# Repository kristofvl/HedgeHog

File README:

More information about this package can currently be found at:
 http://kristofvl.github.io/HedgeHog/ 

****************************************************************

In short, this repository contains three packages:

1. The HedgeHog firmware (operating system), requires:
    - MPLAB X (free IDE, download from Microchip.com)
    - Microchip Application Library (free library set, download 
      from Microchip.com)

2. The HedgeHog Graphical interface software, requires:
    - the basic python libraries
    - matplotlib

3. The hardware design files for the HedgeHog sensor, requires:
    - eagleCAD (free PCB design tool, download from 
      CadSoftusa.com)

****************************************************************

# User Manual

## Setup a new HedgeHog

There are four basic interactions, that you can do with your HedgeHog

	- Configure the HedgeHog
	- Start logging
	- Download the logged data
	- Display the downloaded data

In order to perform this actions, you first need to setupt your PC properly.

	- Clone this repository
	- Execute the command *./install_HHG.py* in *~/HedgeHog/HHG*

This will create a few Desktop shortcuts to scripts, that will be discussed later on.

If you have a brand new HedgeHog, you will need to do some extra adjustments, if not, then just continue at *Configure the HedgeHog*. The following instructions might also help, if there are other issues with the HedgeHog. You need to put the right image on the SD-Card. To do this, put the SD-Card in the SD-Card slot in yout PC. You need to find out, where the SD-Card is mounted (e.g. with *dmesg*). In this example, it is assumed, the SD-Card is mounted at /dev/sdc. Go to the folder *~/HedgeHog/HHG/dd_img/* and execute the commands

	- *sudo dd if=dd.img of=/dev/sdc*
	- *sync*

This will export the correct image to the SD-Card. After exporting the image, disconnect the SD-Card and reconnect it again. If it is named *HEDGHG*, the export was succesfull. Now put your SD-Card into your HedgeHog.

Now you need to flash the HedgeHog with *MPLab*. Make sure to choose the correct hardware profile.

## Configure the HedgeHog

If you plug in the HedgeHog into the USB-Connector of your PC, it should be recognized correctly now. The install command has created a shortcut to the configuration script. Start the script now and choose the configuration you want, then click *configure*. The HedgeHog will unmount and then mount again by itself. As soon as the HedgeHog is mounted again, the configuration is applied.

## Start logging

When the HedgeHog has the right configuration, it is ready to be started. Therefore use the start script, that also was created by the install command. The HedgeHog will be started and will log data, that are stored at the SD-Card. 
Since firmware version 1.4000, the HedgeHog will continue logging, even if it is plugged into the USB-Connector. When plugged in, you can visualize the data, as shown in *Download the logged data* and *Display the downloaded data*. When the HedgeHog is unpluged again, it will continue logging data.

## Download the logged data

To download the logged data, you can use the download script. A shortcut to the script was also created during the installation progress. The data will be saved at *~/hhg_logs/<HHG device number>/<date>/d.npz*

## Display the downloaded data

To visualize the data, a python script is contained in the repository. To use it, the command is
	- *./viz_HHG.py ~/hhg_logs/<HHG device number>/<date>/d.npz* in *~/HedgeHog/HHG*

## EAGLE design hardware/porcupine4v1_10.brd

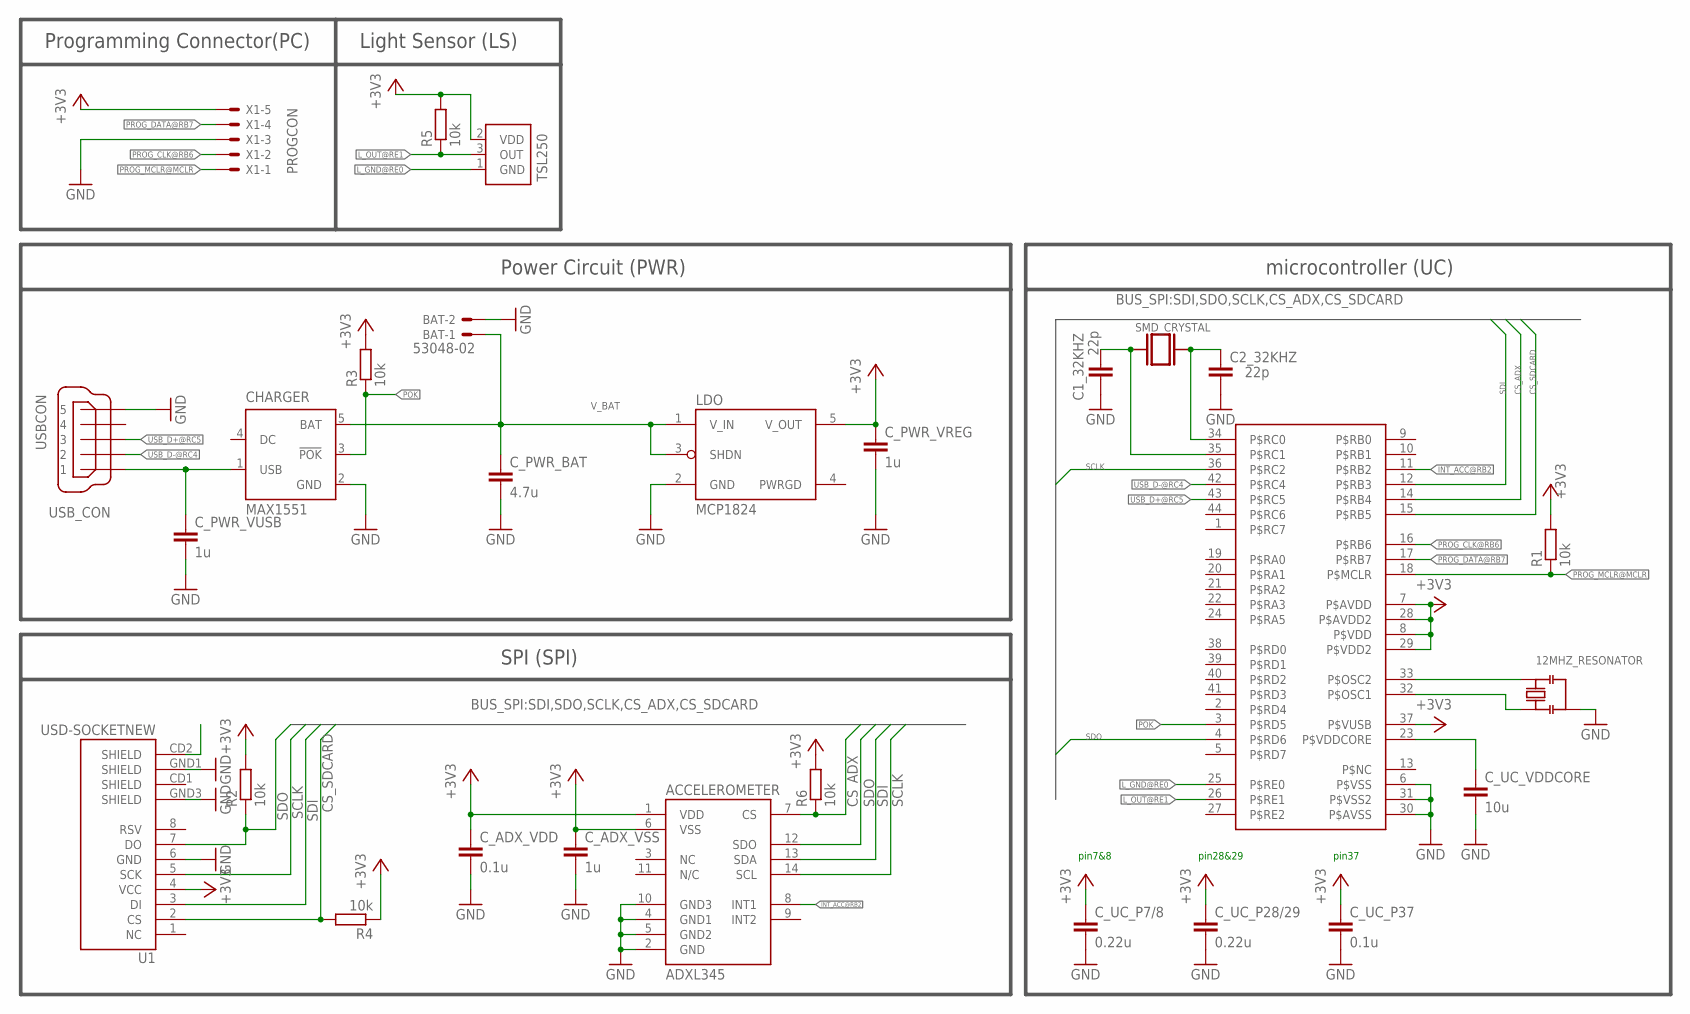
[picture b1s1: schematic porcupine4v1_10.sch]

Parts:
12MHZ_RESONATOR: RESONATORPRQC-C; PRQC-C
32KHZ_CRYSTAL: SMD_CRYSTAL
ACCELEROMETER: ADXL345; LGA14
BAT: 53048-02
C1_32KHZ, C2_32KHZ: 22p; C0603K
CHARGER: MAX1551; SOT23-5L
C_ADX_VDD: 0.1u; C0603K
C_ADX_VSS: 1u; C0603K
C_PWR_BAT: 4.7u; C0603K
C_PWR_VREG: 1u; C0603K
C_PWR_VUSB: 1u; C0603K
C_UC_P7/8, C_UC_P28/29: 0.22u; C0603K
C_UC_P37: 0.1u; C0603K
C_UC_VDDCORE: 10u; C0805K
LDO: MCP1824; SOT-23-5
LIGHTSENSE: TSL250; TSL
PIC_CONTROLLER: PIC_P2V6; QFN44ML8X8
R1, R2, R3, R4, R5, R6: 10k; R0603
U1: USD-SOCKETNEW; MICRO-SD-SOCKET-PP
USB_CON: USBCON; 248601
X1: PROGCON; 53047-05-OCT

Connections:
+3V3: ACCELEROMETER.1 (VDD), ACCELEROMETER.6 (VSS), C_ADX_VDD.1, C_ADX_VSS.1, C_PWR_VREG.1, C_UC_P7/8.1, C_UC_P28/29.1, C_UC_P37.1, LDO.5 (V_OUT), LIGHTSENSE.2 (VDD), PIC_CONTROLLER.7 (P$AVDD), PIC_CONTROLLER.8 (P$VDD), PIC_CONTROLLER.28 (P$AVDD2), PIC_CONTROLLER.29 (P$VDD2), PIC_CONTROLLER.37 (P$VUSB), R1.2, R2.2, R3.2, R4.1, R5.2, R6.2, U1.4 (VCC), X1.5
CS_ADX: ACCELEROMETER.7 (CS), PIC_CONTROLLER.14 (P$RB4), R6.1
CS_SDCARD: PIC_CONTROLLER.15 (P$RB5), R4.2, U1.2 (CS)
GND: 12MHZ_RESONATOR.2_GND (GND), ACCELEROMETER.2 (GND), ACCELEROMETER.4 (GND1), ACCELEROMETER.5 (GND2), ACCELEROMETER.10 (GND3), BAT.2, C1_32KHZ.2, C2_32KHZ.2, CHARGER.2 (GND), C_ADX_VDD.2, C_ADX_VSS.2, C_PWR_BAT.2, C_PWR_VREG.2, C_PWR_VUSB.2, C_UC_P7/8.2, C_UC_P28/29.2, C_UC_P37.2, C_UC_VDDCORE.2, LDO.2 (GND), PIC_CONTROLLER.6 (P$VSS), PIC_CONTROLLER.30 (P$AVSS), PIC_CONTROLLER.31 (P$VSS2), U1.6 (GND), U1.GND1 (SHIELD), U1.GND3 (SHIELD), USB_CON.5, X1.3
INT_ACC@RB2: ACCELEROMETER.8 (INT1), PIC_CONTROLLER.11 (P$RB2)
L_GND@RE0: LIGHTSENSE.1 (GND), PIC_CONTROLLER.25 (P$RE0)
L_OUT@RE1: LIGHTSENSE.3 (OUT), PIC_CONTROLLER.26 (P$RE1), R5.1
unnamed: 12MHZ_RESONATOR.3 (2), PIC_CONTROLLER.32 (P$OSC1)
unnamed: 12MHZ_RESONATOR.1, PIC_CONTROLLER.33 (P$OSC2)
unnamed: 32KHZ_CRYSTAL.P$2 (2), C2_32KHZ.1, PIC_CONTROLLER.34 (P$RC0)
unnamed: 32KHZ_CRYSTAL.P$1 (1), C1_32KHZ.1, PIC_CONTROLLER.35 (P$RC1)
P$RD7: PIC_CONTROLLER.5 (P$RD7)
POK: CHARGER.3 (!POK), PIC_CONTROLLER.3 (P$RD5), R3.1
PROG_CLK@RB6: PIC_CONTROLLER.16 (P$RB6), X1.2
PROG_DATA@RB7: PIC_CONTROLLER.17 (P$RB7), X1.4
PROG_MCLR@MCLR: PIC_CONTROLLER.18 (P$MCLR), R1.1, X1.1
SCLK: ACCELEROMETER.14 (SCL), PIC_CONTROLLER.36 (P$RC2), U1.5 (SCK)
SDI: ACCELEROMETER.13 (SDA), PIC_CONTROLLER.12 (P$RB3), U1.3 (DI)
SDO: ACCELEROMETER.12 (SDO), PIC_CONTROLLER.4 (P$RD6), R2.1, U1.7 (DO)
USB_D+@RC5: PIC_CONTROLLER.43 (P$RC5), USB_CON.3
USB_D-@RC4: PIC_CONTROLLER.42 (P$RC4), USB_CON.2
VDDCORE: C_UC_VDDCORE.1, PIC_CONTROLLER.23 (P$VDDCORE)
V_BAT: BAT.1, CHARGER.5 (BAT), C_PWR_BAT.1, LDO.1 (V_IN), LDO.3 (SHDN)
V_USB: CHARGER.1 (USB), C_PWR_VUSB.1, USB_CON.1

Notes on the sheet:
Programming Connector(PC)
pin28&29
pin37
Power Circuit (PWR)
SPI (SPI)
microcontroller (UC)
Light Sensor (LS)
pin7&8

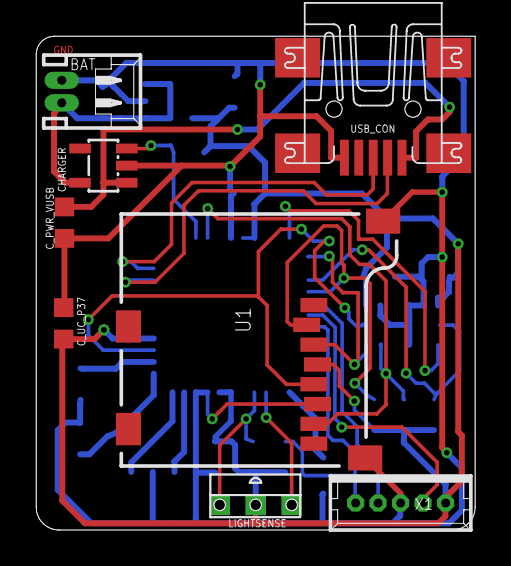
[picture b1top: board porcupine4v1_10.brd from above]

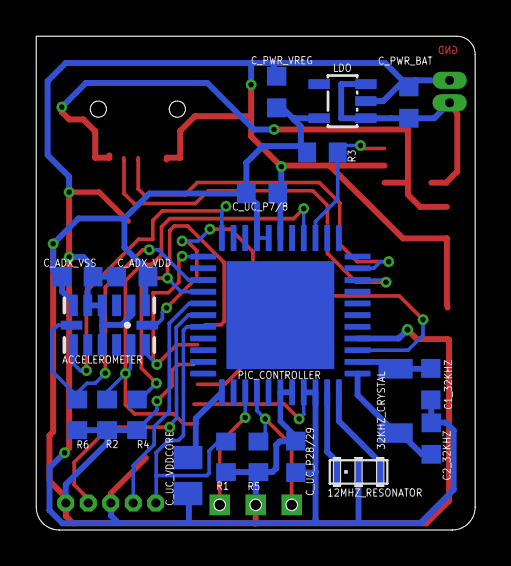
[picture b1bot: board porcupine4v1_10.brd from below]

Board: 2 copper layers, 24.4 x 27.4 mm, 28 parts (20 on the bottom side), 23 nets.

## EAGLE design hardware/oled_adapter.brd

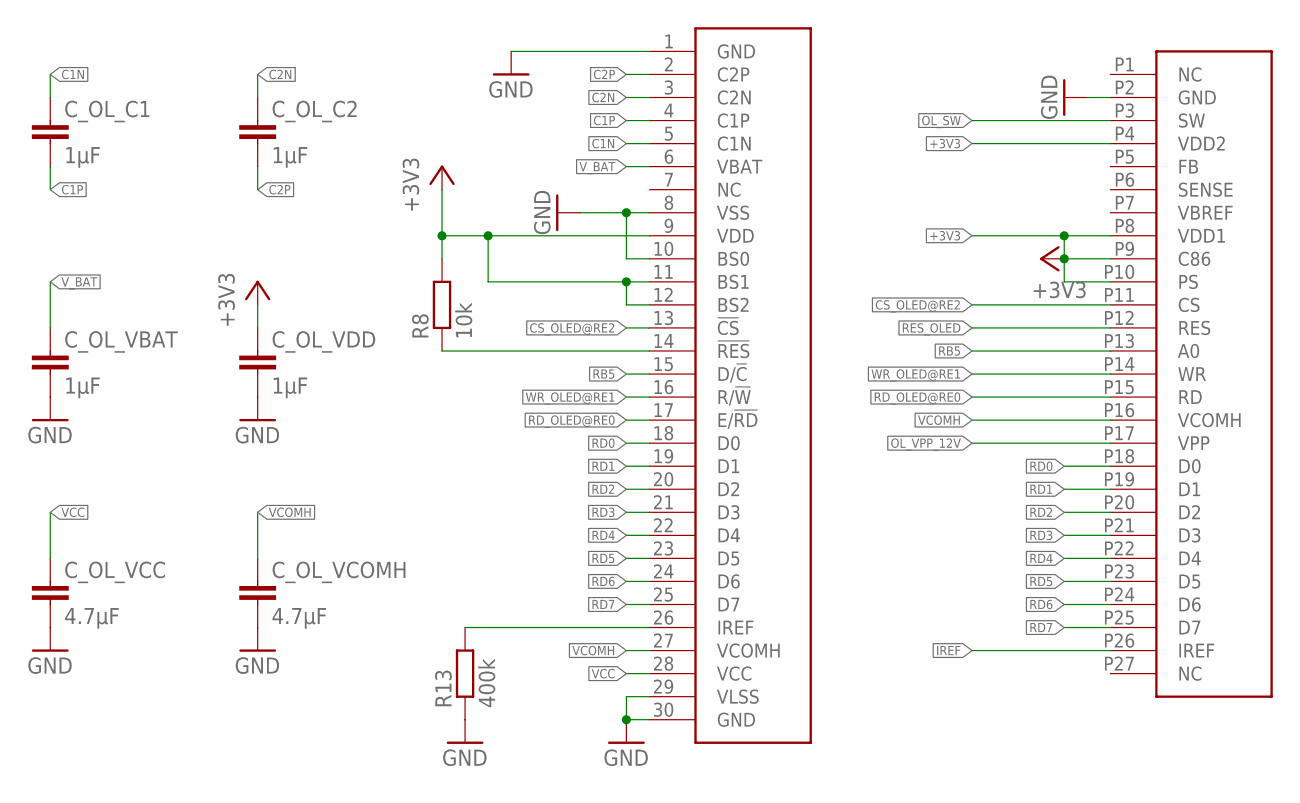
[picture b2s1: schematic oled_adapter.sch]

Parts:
CON_OLED: OLED_DENSITRON; CON_DD-12864WE-1A
C_OL_C1, C_OL_C2: 1µF; C0603K
C_OL_VBAT: 1µF; C0603K
C_OL_VCC: 4.7µF; C0603K
C_OL_VCOMH: 4.7µF; C0603K
C_OL_VDD: 1µF; C0603K
OLED: DD-12864WE-4A; CON_DD-12864WE-4A
R8: 10k; R0603
R13: 400k; R0603

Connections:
+3V3: CON_OLED.P4 (VDD2), CON_OLED.P8 (VDD1), CON_OLED.P9 (C86), CON_OLED.P10 (PS), C_OL_VDD.1, OLED.9 (VDD), OLED.11 (BS1), OLED.12 (BS2), R8.2
C1N: C_OL_C1.1, OLED.5 (C1N)
C1P: C_OL_C1.2, OLED.4 (C1P)
C2N: C_OL_C2.1, OLED.3 (C2N)
C2P: C_OL_C2.2, OLED.2 (C2P)
CS_OLED@RE2: CON_OLED.P11 (CS), OLED.13 (!CS)
GND: CON_OLED.P2 (GND), C_OL_VBAT.2, C_OL_VCC.2, C_OL_VCOMH.2, C_OL_VDD.2, OLED.1 (GND), OLED.8 (VSS), OLED.10 (BS0), OLED.29 (VLSS), OLED.30 (GND), R13.1
IREF: CON_OLED.P26 (IREF), OLED.26 (IREF), R13.2
OL_SW: CON_OLED.P3 (SW)
OL_VPP_12V: CON_OLED.P17 (VPP)
RB5: CON_OLED.P13 (A0), OLED.15 (D/!C)
RD0: CON_OLED.P18 (D0), OLED.18 (D0)
RD1: CON_OLED.P19 (D1), OLED.19 (D1)
RD2: CON_OLED.P20 (D2), OLED.20 (D2)
RD3: CON_OLED.P21 (D3), OLED.21 (D3)
RD4: CON_OLED.P22 (D4), OLED.22 (D4)
RD5: CON_OLED.P23 (D5), OLED.23 (D5)
RD6: CON_OLED.P24 (D6), OLED.24 (D6)
RD7: CON_OLED.P25 (D7), OLED.25 (D7)
RD_OLED@RE0: CON_OLED.P15 (RD), OLED.17 (E/!RD)
RES_OLED: CON_OLED.P12 (RES), OLED.14 (!RES), R8.1
VCC: C_OL_VCC.1, OLED.28 (VCC)
VCOMH: CON_OLED.P16 (VCOMH), C_OL_VCOMH.1, OLED.27 (VCOMH)
V_BAT: C_OL_VBAT.1, OLED.6 (VBAT)
WR_OLED@RE1: CON_OLED.P14 (WR), OLED.16 (R/!W)

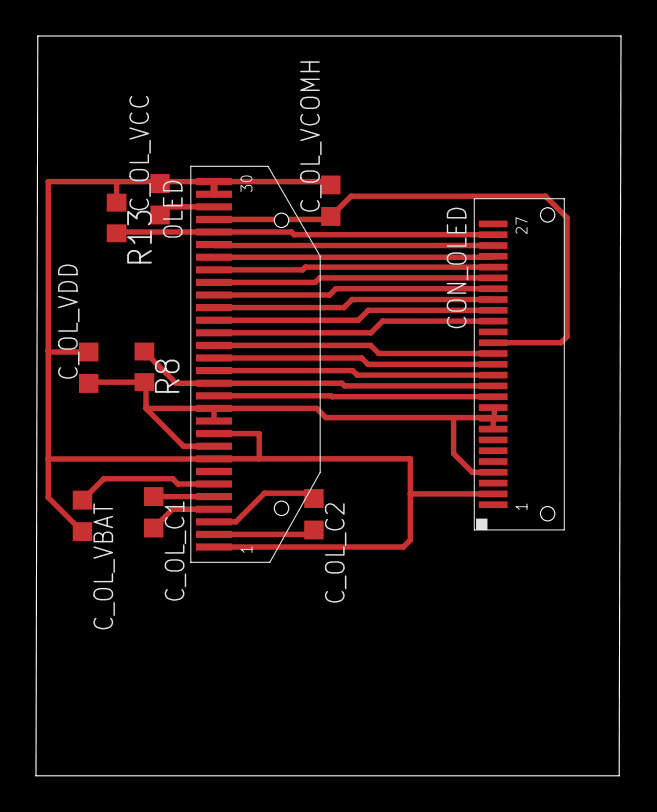
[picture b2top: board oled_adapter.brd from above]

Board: 2 copper layers, 32.5 x 41.1 mm, 10 parts (0 on the bottom side), 23 nets.

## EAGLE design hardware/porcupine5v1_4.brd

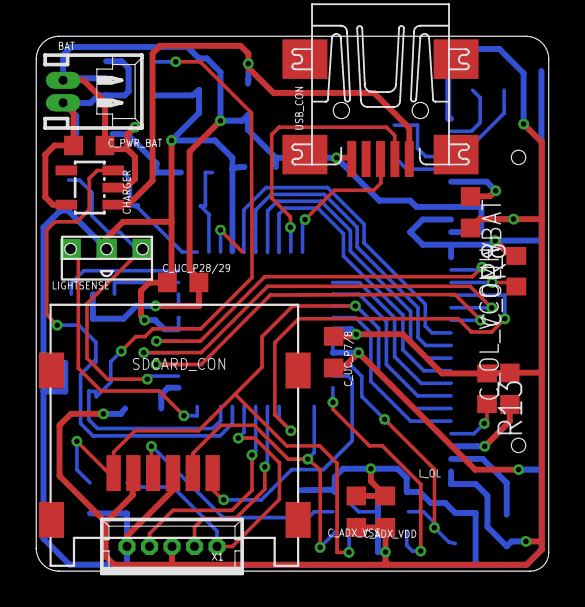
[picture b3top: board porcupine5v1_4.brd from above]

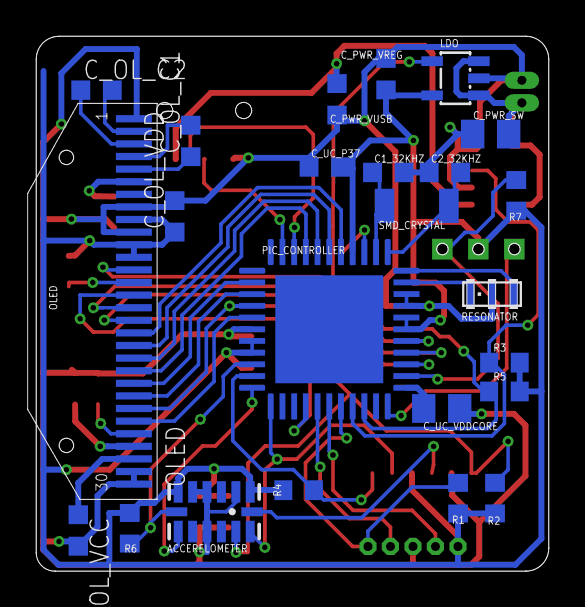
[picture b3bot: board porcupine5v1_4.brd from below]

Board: 2 copper layers, 28.5 x 29.7 mm, 39 parts (24 on the bottom side), 43 nets.

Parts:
12MHZ_RESONATOR: RESONATORPRQC-C; PRQC-C
ACCERELOMETER: ADXL345; LGA14
BAT: 53048-02
C1_32KHZ, C2_32KHZ: 22p; C0603K
CHARGER: MAX1551; SOT23-5L
C_ADX_VDD: 0.1u; C0603K
C_ADX_VSS: 1u; C0603K
C_OL_C1, C_OL_C2: 1µF; C0603K
C_OL_VBAT: 1µF; C0603K
C_OL_VCC: 4.7µF; C0603K
C_OL_VCOMH: 4.7µF; C0603K
C_OL_VDD: 1µF; C0603K
C_PWR_BAT: 1u; C0603K
C_PWR_SW: 10u; C0805K
C_PWR_VREG: 1u; C0603K
C_PWR_VUSB: 1u; C0603K
C_UC_P7/8, C_UC_P28/29: 0.22u; C0603K
C_UC_P37: 0.1u; C0603K
C_UC_VDDCORE: 10u; C0805K
LDO: MCP1824; SOT-23-5
LIGHTSENSE: TSL250; TSL
OLED: DD-12864WE-4A; CON_DD-12864WE-4A
PIC_CONTROLLER: PIC_P2V6; QFN44ML8X8
R1, R2, R3, R4, R5, R6, R7, R8: 10k; R0603
R13: 400k; R0603
SDCARD_CON: MICROSD_CONN; 460DA40013
SMD_CRYSTAL: SMD_CRYSTAL
USB_CON: USBCON; 248601
X1: PROGCON; 53047-05-OCT

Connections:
+3V3: ACCERELOMETER.1, ACCERELOMETER.6, C_ADX_VDD.1, C_ADX_VSS.1, C_OL_VDD.1, C_PWR_VREG.1, C_UC_P7/8.1, C_UC_P28/29.1, C_UC_P37.1, LDO.5, LIGHTSENSE.2, OLED.9, OLED.11, OLED.12, PIC_CONTROLLER.7, PIC_CONTROLLER.8, PIC_CONTROLLER.28, PIC_CONTROLLER.29, PIC_CONTROLLER.37, R1.2, R2.2, R3.2, R4.1, R5.2, R6.2, R7.2, R8.2, SDCARD_CON.P$4, X1.5
C1N: C_OL_C1.1, OLED.5
C1P: C_OL_C1.2, OLED.4
C2N: C_OL_C2.1, OLED.3
C2P: C_OL_C2.2, OLED.2
CS_ADX: ACCERELOMETER.7, PIC_CONTROLLER.9, R6.1
CS_OLED@RE2: OLED.13, PIC_CONTROLLER.27
CS_SDCARD: PIC_CONTROLLER.10, R4.2, SDCARD_CON.P$2
D0_OLED@RD0: OLED.18, PIC_CONTROLLER.38
D1_OLED@RD1: OLED.19, PIC_CONTROLLER.39
D2_OLED@RD2: OLED.20, PIC_CONTROLLER.40
D3_OLED@RD3: OLED.21, PIC_CONTROLLER.41
D4_OLED@RD4: OLED.22, PIC_CONTROLLER.2
D5_OLED@RD5: OLED.23, PIC_CONTROLLER.3
D7_OLED@RD7: OLED.25, PIC_CONTROLLER.5
D/C#_OLED@RB5: OLED.15, PIC_CONTROLLER.15
GND: 12MHZ_RESONATOR.2_GND, ACCERELOMETER.2, ACCERELOMETER.4, ACCERELOMETER.5, ACCERELOMETER.10, BAT.2, C1_32KHZ.2, C2_32KHZ.2, CHARGER.2, C_ADX_VDD.2, C_ADX_VSS.2, C_OL_VBAT.2, C_OL_VCC.2, C_OL_VCOMH.2, C_OL_VDD.2, C_PWR_BAT.2, C_PWR_SW.2, C_PWR_VREG.2, C_PWR_VUSB.2, C_UC_P7/8.2, C_UC_P28/29.2, C_UC_P37.2, C_UC_VDDCORE.2, LDO.2, OLED.1, OLED.8, OLED.10, OLED.29, OLED.30, PIC_CONTROLLER.6, PIC_CONTROLLER.30, PIC_CONTROLLER.31, R13.1, SDCARD_CON.P$6, USB_CON.5, X1.3
INT_ACC@RB2: ACCERELOMETER.8, PIC_CONTROLLER.11
IREF: OLED.26, R13.2
L_GND@RA3: LIGHTSENSE.1, PIC_CONTROLLER.22
L_OUT@RA5: LIGHTSENSE.3, PIC_CONTROLLER.24, R7.1
unnamed: 12MHZ_RESONATOR.1, PIC_CONTROLLER.33
unnamed: 12MHZ_RESONATOR.3, PIC_CONTROLLER.32
unnamed: C2_32KHZ.1, PIC_CONTROLLER.34, SMD_CRYSTAL.P$1
unnamed: C1_32KHZ.1, PIC_CONTROLLER.35, SMD_CRYSTAL.P$2
POK: CHARGER.3, PIC_CONTROLLER.19, R3.1
PROG_CLK@RB6: PIC_CONTROLLER.16, X1.2
PROG_DATA@RB7: PIC_CONTROLLER.17, X1.4
PROG_MCLR@MCLR: PIC_CONTROLLER.18, R1.1, X1.1
PWRGD: LDO.4, PIC_CONTROLLER.20, R5.1
RD_OLED@RE0: OLED.17, PIC_CONTROLLER.25
RES_OLED: OLED.14, R8.1
SCLK: ACCERELOMETER.14, PIC_CONTROLLER.36, SDCARD_CON.P$5
SDI: ACCERELOMETER.13, PIC_CONTROLLER.12, SDCARD_CON.P$3
SDO_SPI&D6_OLED@RD6: ACCERELOMETER.12, OLED.24, PIC_CONTROLLER.4, R2.1, SDCARD_CON.P$7
USB_D+@RC5: PIC_CONTROLLER.43, USB_CON.3
USB_D-@RC4: PIC_CONTROLLER.42, USB_CON.2
VCC: C_OL_VCC.1, OLED.28
VCOMH: C_OL_VCOMH.1, OLED.27
VDDCORE: C_UC_VDDCORE.1, PIC_CONTROLLER.23
VUSB: CHARGER.1, C_PWR_VUSB.1, USB_CON.1
V_BAT: BAT.1, CHARGER.5, C_OL_VBAT.1, C_PWR_BAT.1, C_PWR_SW.1, LDO.1, LDO.3, OLED.6
WR_OLED@RE1: OLED.16, PIC_CONTROLLER.26

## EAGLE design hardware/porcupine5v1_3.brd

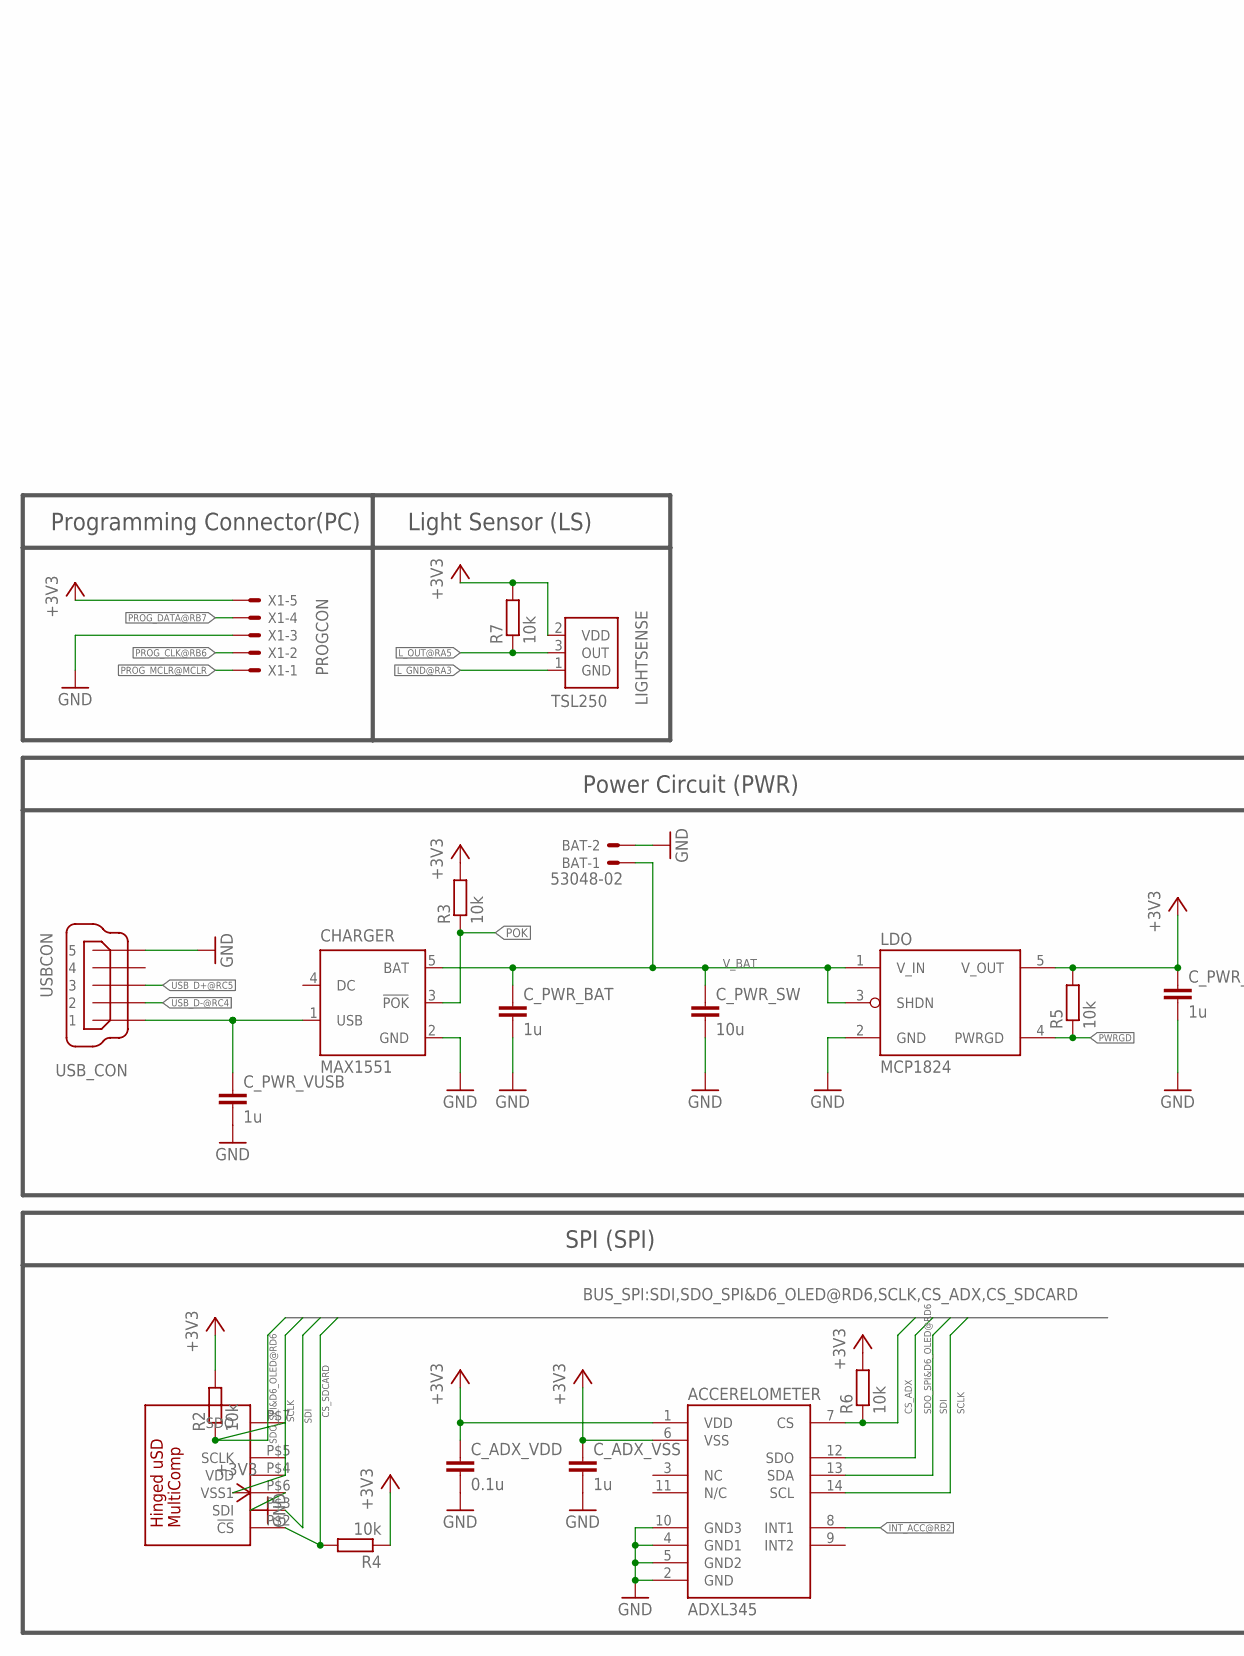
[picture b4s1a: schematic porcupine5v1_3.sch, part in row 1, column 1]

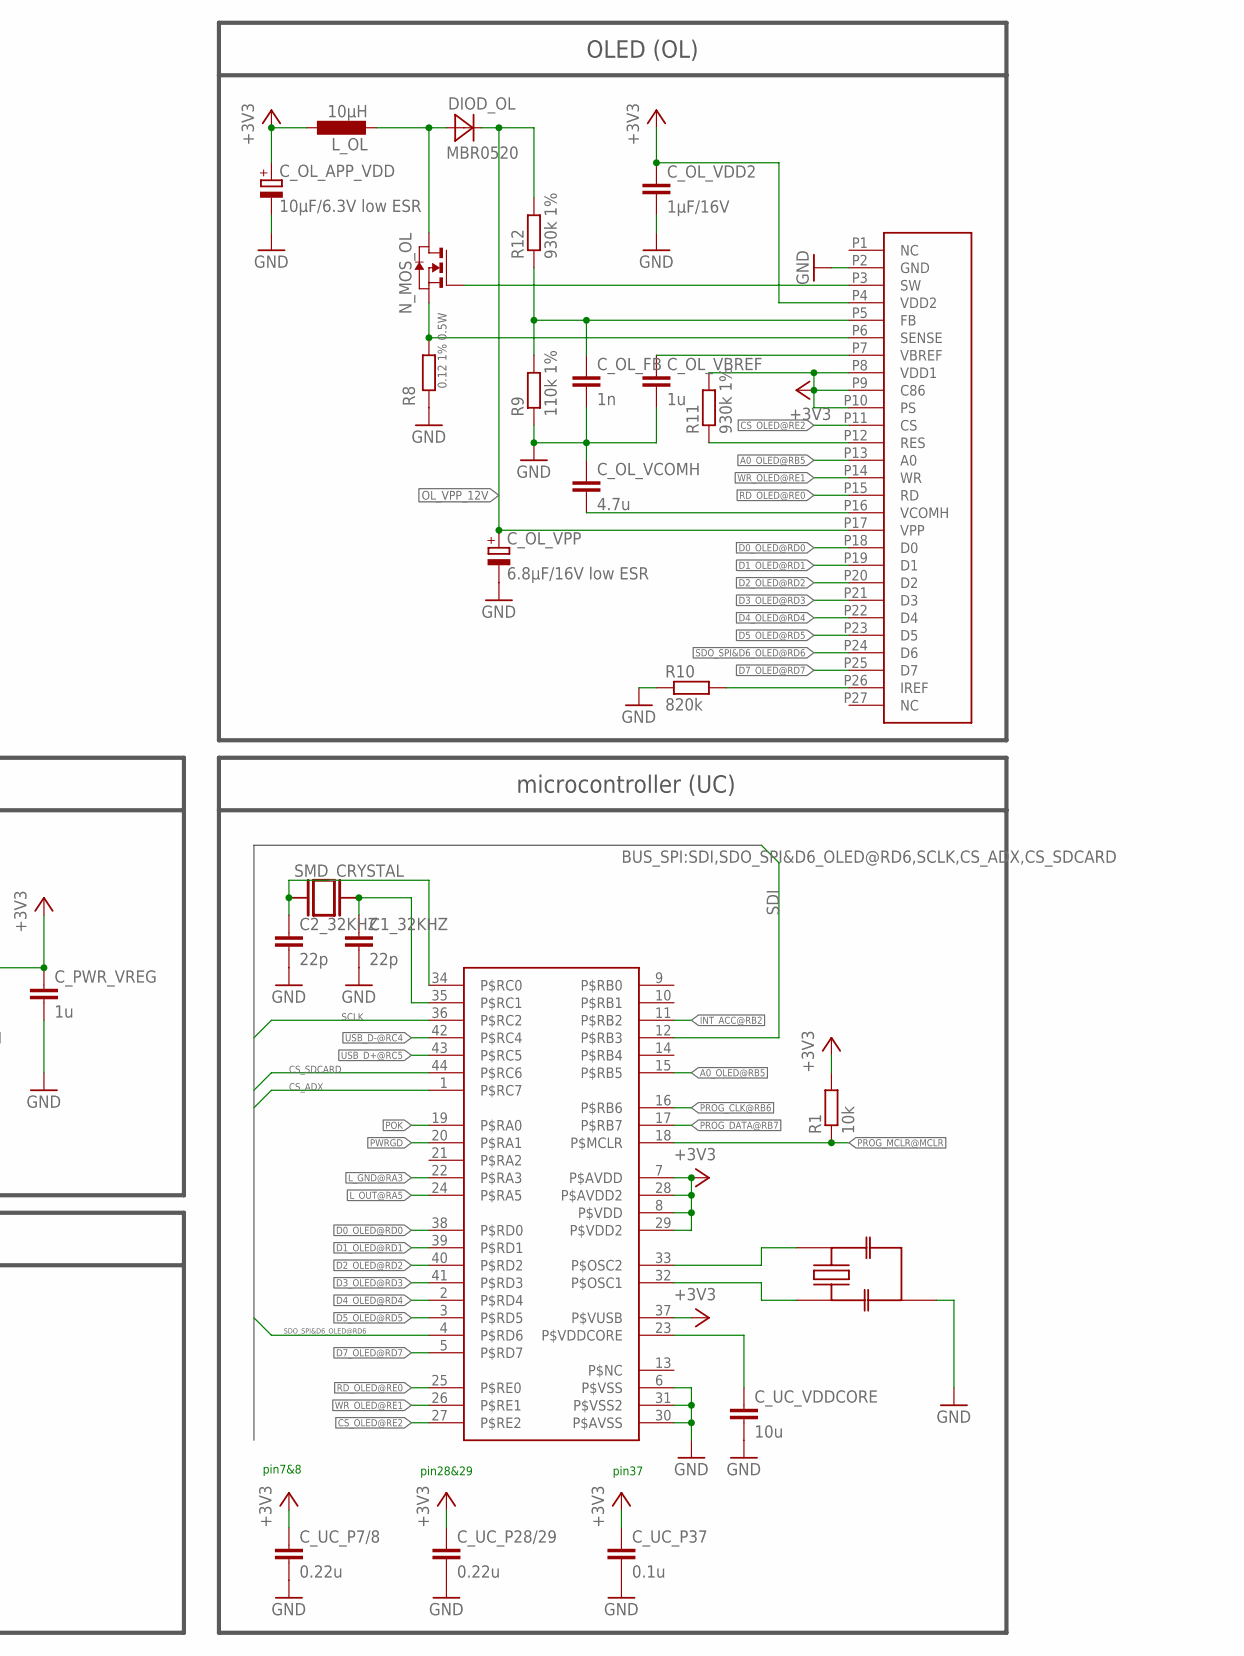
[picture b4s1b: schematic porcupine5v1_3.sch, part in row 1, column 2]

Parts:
ACCERELOMETER: ADXL345; LGA14
BAT: 53048-02
C1_32KHZ, C2_32KHZ: 22p; C0603K
CHARGER: MAX1551; SOT23-5L
CON_OLED: OLED_DENSITRON; CON_DD-12864WE-1A
C_ADX_VDD: 0.1u; C0603K
C_ADX_VSS: 1u; C0603K
C_OL_APP_VDD: 10µF/6.3V low ESR; A/3216-18R
C_OL_FB: 1n; C0603K
C_OL_VBREF: 1u; C0603K
C_OL_VCOMH: 4.7u; C0603K
C_OL_VDD2: 1µF/16V; C0603K
C_OL_VPP: 6.8µF/16V low ESR; A/3216-18R
C_PWR_BAT: 1u; C0603K
C_PWR_SW: 10u; C0805K
C_PWR_VREG: 1u; C0603K
C_PWR_VUSB: 1u; C0603K
C_UC_P7/8, C_UC_P28/29: 0.22u; C0603K
C_UC_P37: 0.1u; C0603K
C_UC_VDDCORE: 10u; C0805K
DIOD_OL: MBR0520; SOD123
LDO: MCP1824; SOT-23-5
LIGHTSENSE: TSL250; TSL
L_OL: 10µH; 1212_FOR_INDUCTANCE
N_MOS_OL: MGSF1N02LT1; SOT-23
PIC_CONTROLLER: PIC_P2V6; QFN44ML8X8
R1, R2, R3, R4, R5, R6, R7: 10k; R0603
R8: 0.12 1% 0.5W; 0805_UPSIDEDOWN
R9: 110k 1%; R0603
R10: 820k; R0603
R11, R12: 930k 1%; R0603
RESONATOR: RESONATORPRQC-S; PRQC
SDCARD_CON: MICROSD_CONN; 460DA40013
SMD_CRYSTAL: SMD_CRYSTAL
USB_CON: USBCON; 248601
X1: PROGCON; 53047-05-OCT

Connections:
+3V3: ACCERELOMETER.1 (VDD), ACCERELOMETER.6 (VSS), CON_OLED.P4 (VDD2), CON_OLED.P8 (VDD1), CON_OLED.P9 (C86), CON_OLED.P10 (PS), C_ADX_VDD.1, C_ADX_VSS.1, C_OL_APP_VDD.+, C_OL_VDD2.2, C_PWR_VREG.1, C_UC_P7/8.1, C_UC_P28/29.1, C_UC_P37.1, LDO.5 (V_OUT), LIGHTSENSE.2 (VDD), L_OL.P$1 (1), PIC_CONTROLLER.7 (P$AVDD), PIC_CONTROLLER.8 (P$VDD), PIC_CONTROLLER.28 (P$AVDD2), PIC_CONTROLLER.29 (P$VDD2), PIC_CONTROLLER.37 (P$VUSB), R1.2, R2.2, R3.2, R4.1, R5.2, R6.2, R7.2, R11.2, SDCARD_CON.P$4 (VDD), X1.5
A0_OLED@RB5: CON_OLED.P13 (A0), PIC_CONTROLLER.15 (P$RB5)
CS_ADX: ACCERELOMETER.7 (CS), PIC_CONTROLLER.1 (P$RC7), R6.1
CS_OLED@RE2: CON_OLED.P11 (CS), PIC_CONTROLLER.27 (P$RE2)
CS_SDCARD: PIC_CONTROLLER.44 (P$RC6), R4.2, SDCARD_CON.P$2 (!CS)
D0_OLED@RD0: CON_OLED.P18 (D0), PIC_CONTROLLER.38 (P$RD0)
D1_OLED@RD1: CON_OLED.P19 (D1), PIC_CONTROLLER.39 (P$RD1)
D2_OLED@RD2: CON_OLED.P20 (D2), PIC_CONTROLLER.40 (P$RD2)
D3_OLED@RD3: CON_OLED.P21 (D3), PIC_CONTROLLER.41 (P$RD3)
D4_OLED@RD4: CON_OLED.P22 (D4), PIC_CONTROLLER.2 (P$RD4)
D5_OLED@RD5: CON_OLED.P23 (D5), PIC_CONTROLLER.3 (P$RD5)
D7_OLED@RD7: CON_OLED.P25 (D7), PIC_CONTROLLER.5 (P$RD7)
GND: ACCERELOMETER.2 (GND), ACCERELOMETER.4 (GND1), ACCERELOMETER.5 (GND2), ACCERELOMETER.10 (GND3), BAT.2, C1_32KHZ.2, C2_32KHZ.2, CHARGER.2 (GND), CON_OLED.P2 (GND), C_ADX_VDD.2, C_ADX_VSS.2, C_OL_APP_VDD.-, C_OL_FB.2, C_OL_VBREF.2, C_OL_VCOMH.1, C_OL_VDD2.1, C_OL_VPP.-, C_PWR_BAT.2, C_PWR_SW.2, C_PWR_VREG.2, C_PWR_VUSB.2, C_UC_P7/8.2, C_UC_P28/29.2, C_UC_P37.2, C_UC_VDDCORE.2, LDO.2 (GND), PIC_CONTROLLER.6 (P$VSS), PIC_CONTROLLER.30 (P$AVSS), PIC_CONTROLLER.31 (P$VSS2), R8.P$2 (1), R9.1, R10.1, RESONATOR.GND, SDCARD_CON.P$6 (VSS1), USB_CON.5, X1.3
INT_ACC@RB2: ACCERELOMETER.8 (INT1), PIC_CONTROLLER.11 (P$RB2)
L_GND@RA3: LIGHTSENSE.1 (GND), PIC_CONTROLLER.22 (P$RA3)
L_OUT@RA5: LIGHTSENSE.3 (OUT), PIC_CONTROLLER.24 (P$RA5), R7.1
unnamed: PIC_CONTROLLER.33 (P$OSC2), RESONATOR.1
unnamed: PIC_CONTROLLER.32 (P$OSC1), RESONATOR.2
unnamed: C2_32KHZ.1, PIC_CONTROLLER.34 (P$RC0), SMD_CRYSTAL.P$1 (1)
unnamed: C1_32KHZ.1, PIC_CONTROLLER.35 (P$RC1), SMD_CRYSTAL.P$2 (2)
unnamed: DIOD_OL.A, L_OL.P$2 (2), N_MOS_OL.1 (D)
OL_FB: CON_OLED.P5 (FB), C_OL_FB.1, R9.2, R12.1
OL_IREF: CON_OLED.P26 (IREF), R10.2
OL_SENSE: CON_OLED.P6 (SENSE), N_MOS_OL.2 (S), R8.P$3 (2)
OL_SW: CON_OLED.P3 (SW), N_MOS_OL.3 (G)
OL_VBREF: CON_OLED.P7 (VBREF), C_OL_VBREF.1
OL_VCOMH: CON_OLED.P16 (VCOMH), C_OL_VCOMH.2
OL_VPP_12V: CON_OLED.P17 (VPP), C_OL_VPP.+, DIOD_OL.C, R12.2
POK: CHARGER.3 (!POK), PIC_CONTROLLER.19 (P$RA0), R3.1
PROG_CLK@RB6: PIC_CONTROLLER.16 (P$RB6), X1.2
PROG_DATA@RB7: PIC_CONTROLLER.17 (P$RB7), X1.4
PROG_MCLR@MCLR: PIC_CONTROLLER.18 (P$MCLR), R1.1, X1.1
PWRGD: LDO.4 (PWRGD), PIC_CONTROLLER.20 (P$RA1), R5.1
RD_OLED@RE0: CON_OLED.P15 (RD), PIC_CONTROLLER.25 (P$RE0)
RES_OLED: CON_OLED.P12 (RES), R11.1
SCLK: ACCERELOMETER.14 (SCL), PIC_CONTROLLER.36 (P$RC2), SDCARD_CON.P$5 (SCLK)
SDI: ACCERELOMETER.13 (SDA), PIC_CONTROLLER.12 (P$RB3), SDCARD_CON.P$3 (SDI)
SDO_SPI&D6_OLED@RD6: ACCERELOMETER.12 (SDO), CON_OLED.P24 (D6), PIC_CONTROLLER.4 (P$RD6), R2.1, SDCARD_CON.P$7 (SDO)
USB_D+@RC5: PIC_CONTROLLER.43 (P$RC5), USB_CON.3
USB_D-@RC4: PIC_CONTROLLER.42 (P$RC4), USB_CON.2
VDDCORE: C_UC_VDDCORE.1, PIC_CONTROLLER.23 (P$VDDCORE)
VUSB: CHARGER.1 (USB), C_PWR_VUSB.1, USB_CON.1
V_BAT: BAT.1, CHARGER.5 (BAT), C_PWR_BAT.1, C_PWR_SW.1, LDO.1 (V_IN), LDO.3 (SHDN)
WR_OLED@RE1: CON_OLED.P14 (WR), PIC_CONTROLLER.26 (P$RE1)

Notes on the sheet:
Programming Connector(PC)
pin7&8
pin28&29
pin37
Power Circuit (PWR)
SPI (SPI)
OLED (OL)
microcontroller (UC)
Light Sensor (LS)

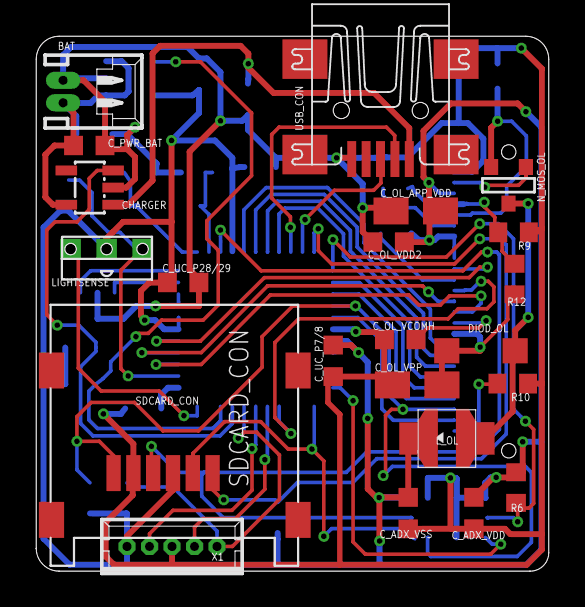
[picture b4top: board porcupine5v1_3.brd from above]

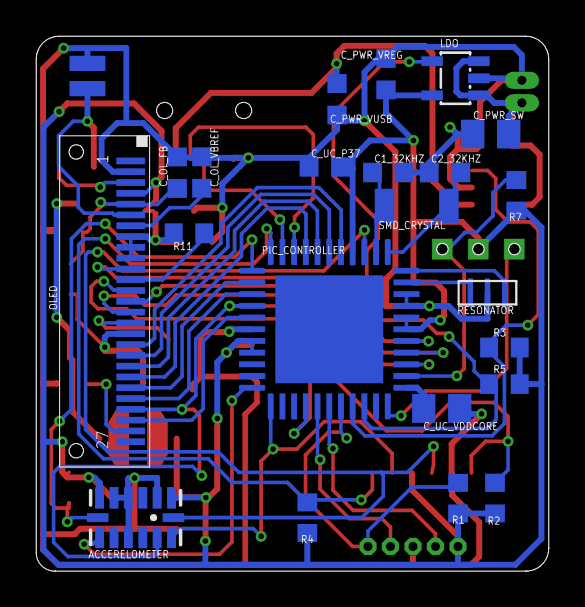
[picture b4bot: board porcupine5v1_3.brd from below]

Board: 2 copper layers, 28.5 x 29.7 mm, 45 parts (23 on the bottom side), 44 nets.

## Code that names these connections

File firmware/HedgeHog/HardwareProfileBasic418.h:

/********************************************************************
 FileName:     	HardwareProfileBasicNew.h
 Dependencies:
 Processor:	PIC18F46J50
 Hardware:	Porcupine HedgeHog BASIC
 Compiler:  	Microchip C18
 Author:        EBerlin
 ********************************************************************/

#ifndef HARDWARE_PROFILE_HEDGEHOG_BASIC_418_H
#define HARDWARE_PROFILE_HEDGEHOG_BASIC_418_H

/*******************************************************************/
/******** Board-specific definitions *******************************/
/*******************************************************************/
#define CLKFREQ_LOG 8000000
#define CLKFREQ_USB 48000000

extern char is_logging;

// used for some of the time-out counters:
#define GetInstructionClock() ((is_logging)?CLKFREQ_LOG:CLKFREQ_USB)
#define GetSystemClock() (CLKFREQ_USB)

//#define DISPLAY_ENABLED		// don't use the oled display
//#define SOFTSTART_ENABLED		// don't use the softstart circuit
#define ADXL345_ENABLED			// use the ADXL345 accelerometer
//#define BMA150_ENABLED		// don't use BMA150 accelerometer

/*******************************************************************/
/******** USB stack hardware selection options *********************/
/*******************************************************************/
// definitions required by the MCHPFSUSB framework. 
//#define USE_SELF_POWER_SENSE_IO
#define tris_self_power		TRISCbits.TRISC2    // Input
#define self_power			1
//#define USE_USB_BUS_SENSE_IO
#define tris_usb_bus_sense	TRISCbits.TRISC2    // Input
#define USB_BUS_SENSE		1

/*******************************************************************/
/******** SPI interface definitions ********************************/
/*******************************************************************/
#define SPICLOCK			TRISCbits.TRISC2
#define SPIIN				TRISDbits.TRISD6
#define SPIOUT				TRISBbits.TRISB3
#define SPICLOCKLAT			LATCbits.LATC2	// Latch pins SCK/SDI/SDO
#define SPIINLAT			LATDbits.LATD6
#define SPIOUTLAT			LATBbits.LATB3
#define SPICLOCKPORT		PORTCbits.RC2	// Port pins SCK/SDI/SDO
#define SPIINPORT			PORTDbits.RD6
#define SPIOUTPORT			PORTBbits.RB3
#define SPICON1				SSP2CON1		// Registers SPI module
#define SPISTAT				SSP2STAT
#define SPIBUF				SSP2BUF
#define SPISTAT_RBF			SSP2STATbits.BF
#define SPICON1bits			SSP2CON1bits
#define SPISTATbits			SSP2STATbits
#define SPI_INTERRUPT_FLAG	PIR3bits.SSP2IF
#define SPIENABLE			SSP2CON1bits.SSPEN

/*******************************************************************/
/******** MDD File System selection options ************************/
/*******************************************************************/
#define USE_PIC18                               // used by FSConfig.h
#define USE_SD_INTERFACE_WITH_SPI
#define SD_CS				PORTBbits.RB5       // Chip Select
#define SD_CS_TRIS			TRISBbits.TRISB5
#define SD_CD				0                   // Card Detect
#define SD_CD_TRIS			TRISAbits.TRISA3
#define SD_WE				0
#define SD_WE_TRIS			TRISAbits.TRISA3
#define SPI_INTERRUPT_FLAG_ASM PIR3, 7

/*******************************************************************/
/******** Accelerometer definitions and options ********************/
/*******************************************************************/
#define ACC_CS				LATBbits.LATB4
#define ACC_CS_TRIS			TRISBbits.TRISB4	// OUTPUT
#define ACC_INT				PORTBbits.RB2
#define ACC_INT_TRIS		TRISBbits.TRISB2	// INPUT

/*******************************************************************/
/******** Power Circuit sense pins definitions and options *********/
/*******************************************************************/
#define USBP_INT_TRIS		TRISDbits.TRISD5   // POK_INT_TRIS = charger "POK"
#define USBP_INT			PORTDbits.RD5      // POK_INT
#define PWRGD_INT_TRIS		TRISDbits.TRISD4   // Voltage converter "power good"
#define PWRGD_INT			PORTDbits.RD4      // PWRGD_INT

/*******************************************************************/
/******** Light Sensor definitions and options *********************/
/*******************************************************************/
#define LIGHTCHANNEL		6					// CHS=6 == AN6 == RE1 (PIN26)
#define LIGHT_PWR			LATEbits.LATE0		// RE0          == RE0 (PIN25)

/*******************************************************************/
/******** remap pins ***********************************************/
/*******************************************************************/
#define ul_reg()	{ EECON2 = 0x55; EECON2 = 0xAA; PPSCONbits.IOLOCK = 0; }
#define l_reg()		{ EECON2 = 0x55; EECON2 = 0xAA; PPSCONbits.IOLOCK = 1; }
// RP6 as SDO2 (o/p), RP13 as SCK2 (o/p), RP23 as SDI2 (i/P), RP5(B2) as INT1
#define remap_pins() {ul_reg();RPOR6=9;RPOR13=10;RPINR21=23;RPINR1=5;l_reg();}

// set pins to input: B2 (acc INT) | D5 (POK) | D4 (PWRGD) | D6 (SPIIN)
#define set_unused_pins_to_output() {TRISA=0;TRISB=0b00000100;TRISD=0b01110000;}

#endif  //HARDWARE_PROFILE_HEDGEHOG_BASIC_418_H
 

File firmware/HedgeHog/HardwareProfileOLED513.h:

/********************************************************************
 FileName:     	HardwareProfileOLED.h
 Dependencies:
 Processor:	PIC18F46J50
 Hardware:	Porcupine HedgeHog OLED
 Compiler:  	Microchip C18
 Author:        KristofVL
 ********************************************************************/

#ifndef HARDWARE_PROFILE_HEDGEHOG_OLED_513_H
#define HARDWARE_PROFILE_HEDGEHOG_OLED_513_H

/*******************************************************************/
/******** Board-specific definitions *******************************/
/*******************************************************************/
#define CLKFREQ_LOG 8000000
#define CLKFREQ_USB 48000000

extern char is_logging;

// used for some of the time-out counters:
#define GetInstructionClock() ((is_logging)?CLKFREQ_LOG:CLKFREQ_USB)
#define GetSystemClock() (CLKFREQ_USB)

#define DISPLAY_ENABLED			// use the oled display
//#define SOFTSTART_ENABLED		// don't use the softstart circuit
#define ADXL345_ENABLED			// use the ADXL345 accelerometer
//#define BMA150_ENABLED		// don't use BMA150 accelerometer

/*******************************************************************/
/******** USB stack hardware selection options *********************/
/*******************************************************************/
// definitions required by the MCHPFSUSB framework. 
//#define USE_SELF_POWER_SENSE_IO
#define tris_self_power		TRISCbits.TRISC2    // Input
#define self_power			1
//#define USE_USB_BUS_SENSE_IO
#define tris_usb_bus_sense	TRISCbits.TRISC2    // Input
#define USB_BUS_SENSE		1

/*******************************************************************/
/******** Bootloader-compatible HEX file ***************************/
/*******************************************************************/
//Uncomment this to make the output HEX of this project 
//   to be able to be bootloaded using the HID bootloader
//#define PROGRAMMABLE_WITH_USB_HID_BOOTLOADER		

/*******************************************************************/
/******** SPI interface definitions ********************************/
/*******************************************************************/
#define SPICLOCK			TRISCbits.TRISC2
#define SPIIN				TRISDbits.TRISD6
#define SPIOUT				TRISBbits.TRISB3
#define SPICLOCKLAT			LATCbits.LATC2	// Latch pins SCK/SDI/SDO
#define SPIINLAT			LATDbits.LATD6
#define SPIOUTLAT			LATBbits.LATB3
#define SPICLOCKPORT		PORTCbits.RC2	// Port pins SCK/SDI/SDO
#define SPIINPORT			PORTDbits.RD6
#define SPIOUTPORT			PORTBbits.RB3
#define SPICON1				SSP2CON1		// Registers SPI module
#define SPISTAT				SSP2STAT
#define SPIBUF				SSP2BUF
#define SPISTAT_RBF			SSP2STATbits.BF
#define SPICON1bits			SSP2CON1bits
#define SPISTATbits			SSP2STATbits
#define SPI_INTERRUPT_FLAG	PIR3bits.SSP2IF
#define SPIENABLE			SSP2CON1bits.SSPEN

/*******************************************************************/
/******** MDD File System selection options ************************/
/*******************************************************************/
#define USE_PIC18			// used by FSConfig.h
#define USE_SD_INTERFACE_WITH_SPI
#define TRIS_CARD_DETECT    TRISBbits.TRISB4    // Input
#define CARD_DETECT         PORTBbits.RB4
#define TRIS_WRITE_DETECT   TRISAbits.TRISA2    // Input
#define SD_CS               PORTCbits.RC6	// Chip Select
#define SD_CS_TRIS          TRISCbits.TRISC6
#define SD_CD               0 //PORTBbits.RB4	// Card detect
#define SD_CD_TRIS          TRISBbits.TRISB4
#define WRITE_DETECT        PORTAbits.RA2	// Write protect
#define SD_WE               PORTAbits.RA2
#define SD_WE_TRIS          TRISAbits.TRISA2
#define SPI_INTERRUPT_FLAG_ASM PIR3, 7

/*******************************************************************/
/******** OLED display selection options    ************************/
/*******************************************************************/
#define	oledWR			LATEbits.LATE1
#define	oledWR_TRIS		TRISEbits.TRISE1
#define	oledRD			LATEbits.LATE0
#define	oledRD_TRIS		TRISEbits.TRISE0
#define	oledCS			LATEbits.LATE2
#define	oledCS_TRIS		TRISEbits.TRISE2
#define	oledRESET		LATDbits.LATD1
#define	oledRESET_TRIS	TRISDbits.TRISD1
#define	oledD_C			LATBbits.LATB5
#define	oledD_C_TRIS	TRISBbits.TRISB5
// Definitions for reset pin (from oled.h)
#define RST_TRIS_BIT	TRISDbits.TRISD2
#define RST_LAT_BIT		LATDbits.LATD2

/*******************************************************************/
/******** Accelerometer definitions and options ********************/
/*******************************************************************/
#define ACC_CS			LATCbits.LATC7
#define ACC_CS_TRIS		TRISCbits.TRISC7
#define ACC_INT			PORTBbits.RB2
#define ACC_INT_TRIS	TRISBbits.TRISB2

/*******************************************************************/
/******** Power Circuit sense pins definitions and options *********/
/*******************************************************************/
#define USBP_INT_TRIS	TRISAbits.TRISA0   // POK_INT_TRIS = charger "POK"
#define USBP_INT		PORTAbits.RA0      // POK_INT
// #define PWRGD_INT_TRIS	TRISAbits.TRISA1   // Voltage converter "power good"
// #define PWRGD_INT		PORTAbits.RA1      // PWRGD_INT

/*******************************************************************/
/******** Light Sensor definitions and options *********************/
/*******************************************************************/
#define LIGHTCHANNEL	4						// RA5 == AN4 == CHANNEL#4
#define LIGHT_PWR		PORTAbits.RA3			// RA3 (PIN22)
#define LIGHT_PWR_TRIS	TRISAbits.RA3

/*******************************************************************/
/******** remap pins ***********************************************/
/*******************************************************************/
#define ul_reg()	{ EECON2 = 0x55; EECON2 = 0xAA; PPSCONbits.IOLOCK = 0;}
#define l_reg()		{ EECON2 = 0x55; EECON2 = 0xAA; PPSCONbits.IOLOCK = 1;}
//  RP6 as SDO2 (o/p), RP13 as SCK2 (o/p), RP23 as SDI2 (i/P),
#define remap_pins() {ul_reg(); RPOR6=9;RPOR13=10;RPINR21=23;RPINR1=5; l_reg();}

// make sure all (unused) pins are output, except for
//  A0 (POK)  -  A1 (PWRGD)  -  A3 (Light GND)  -  A5 (Light Sensor Values)
//	B2 (ACC INT)  -  D6 (SPI MISO)  //0b00100011;
#define set_unused_pins_to_output() { \
	TRISAbits.TRISA0=1;TRISAbits.TRISA1=1;TRISAbits.TRISA2=0;TRISAbits.TRISA3=0;\
	TRISAbits.TRISA5=1; TRISB=0b00000100; TRISD=0; \
}

#endif  //HARDWARE_PROFILE_HEDGEHOG_OLED_513_H

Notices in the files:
parts and their libraries:
SparkFun-Connectors: Licensing: Creative Commons ShareAlike 4.0 International - https://creativecommons.org/licenses/by-sa/4.0
